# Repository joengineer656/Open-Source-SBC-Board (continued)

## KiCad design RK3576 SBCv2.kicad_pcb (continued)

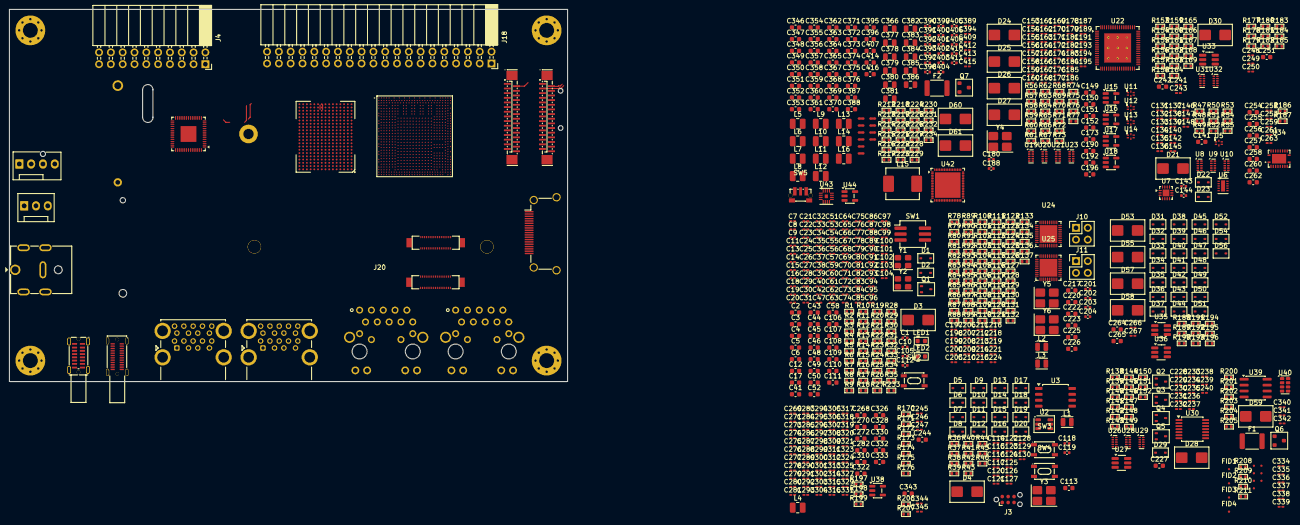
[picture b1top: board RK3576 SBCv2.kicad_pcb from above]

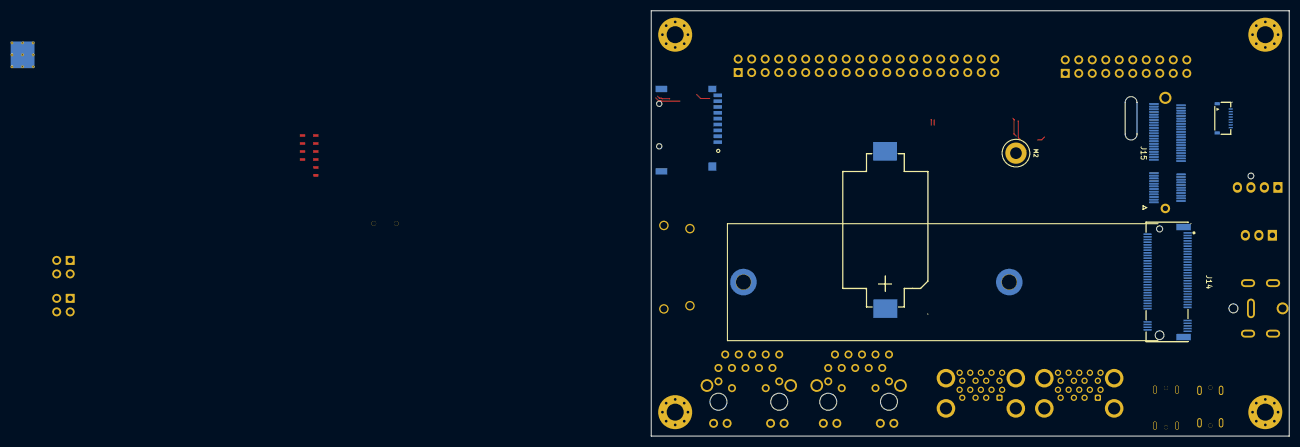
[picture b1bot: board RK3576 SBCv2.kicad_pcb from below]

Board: 8 copper layers, 120.0 x 80.0 mm, 840 parts (4 on the bottom side), 618 nets.

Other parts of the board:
C334, C335, C336, C337, C338, C339: 1u; C_0201_0603Metric_Pad0.64x0.40mm_HandSolder
J20: 513383474; SBC_UFS_EMMC_2x513383474

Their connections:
/RK3576 SOC/FSPI0_CLE/EMMC_DATA_STROBE: J20.23 (eMMC_DATA_STROBE); also elsewhere on the board
/RK3576 SOC/FSPI0_DS/EMMC_CLK_OUT: J20.12 (eMMC_CLKOUT); also elsewhere on the board
/RK3576 SOC/FSPI0_WPn/EMMC_nRST: J20.25 (~eMMC_RSTn); also elsewhere on the board
/RK3576 SOC/UFS.RX0_N: J20.60 (UFS_RX0_N); also elsewhere on the board
/RK3576 SOC/UFS.RX0_P: J20.61 (UFS_RX0_P); also elsewhere on the board
/RK3576 SOC/UFS.RX1_N: J20.57 (UFS_RX1_N); also elsewhere on the board
/RK3576 SOC/UFS.RX1_P: J20.58 (UFS_RX1_P); also elsewhere on the board
/RK3576 SOC/UFS.TX0_N: J20.66 (UFS_TX0_N); also elsewhere on the board
/RK3576 SOC/UFS.TX0_P: J20.67 (UFS_TX0_P); also elsewhere on the board
/RK3576 SOC/UFS.TX1_N: J20.63 (UFS_TX1_N); also elsewhere on the board
/RK3576 SOC/UFS.TX1_P: J20.64 (UFS_TX1_P); also elsewhere on the board
/RK3576 SOC/UFS_REF_{CLK}: J20.42 (UFS_REFCLK); also elsewhere on the board
/RK3576 SOC/UFS_nRST: J20.55 (~UFS_RSTn); also elsewhere on the board
VDDA_1V2_S0: C334.1, C335.1, J20.53 (VCC_1V2_UFS), J20.54 (VCC_1V2_UFS); also elsewhere on the board

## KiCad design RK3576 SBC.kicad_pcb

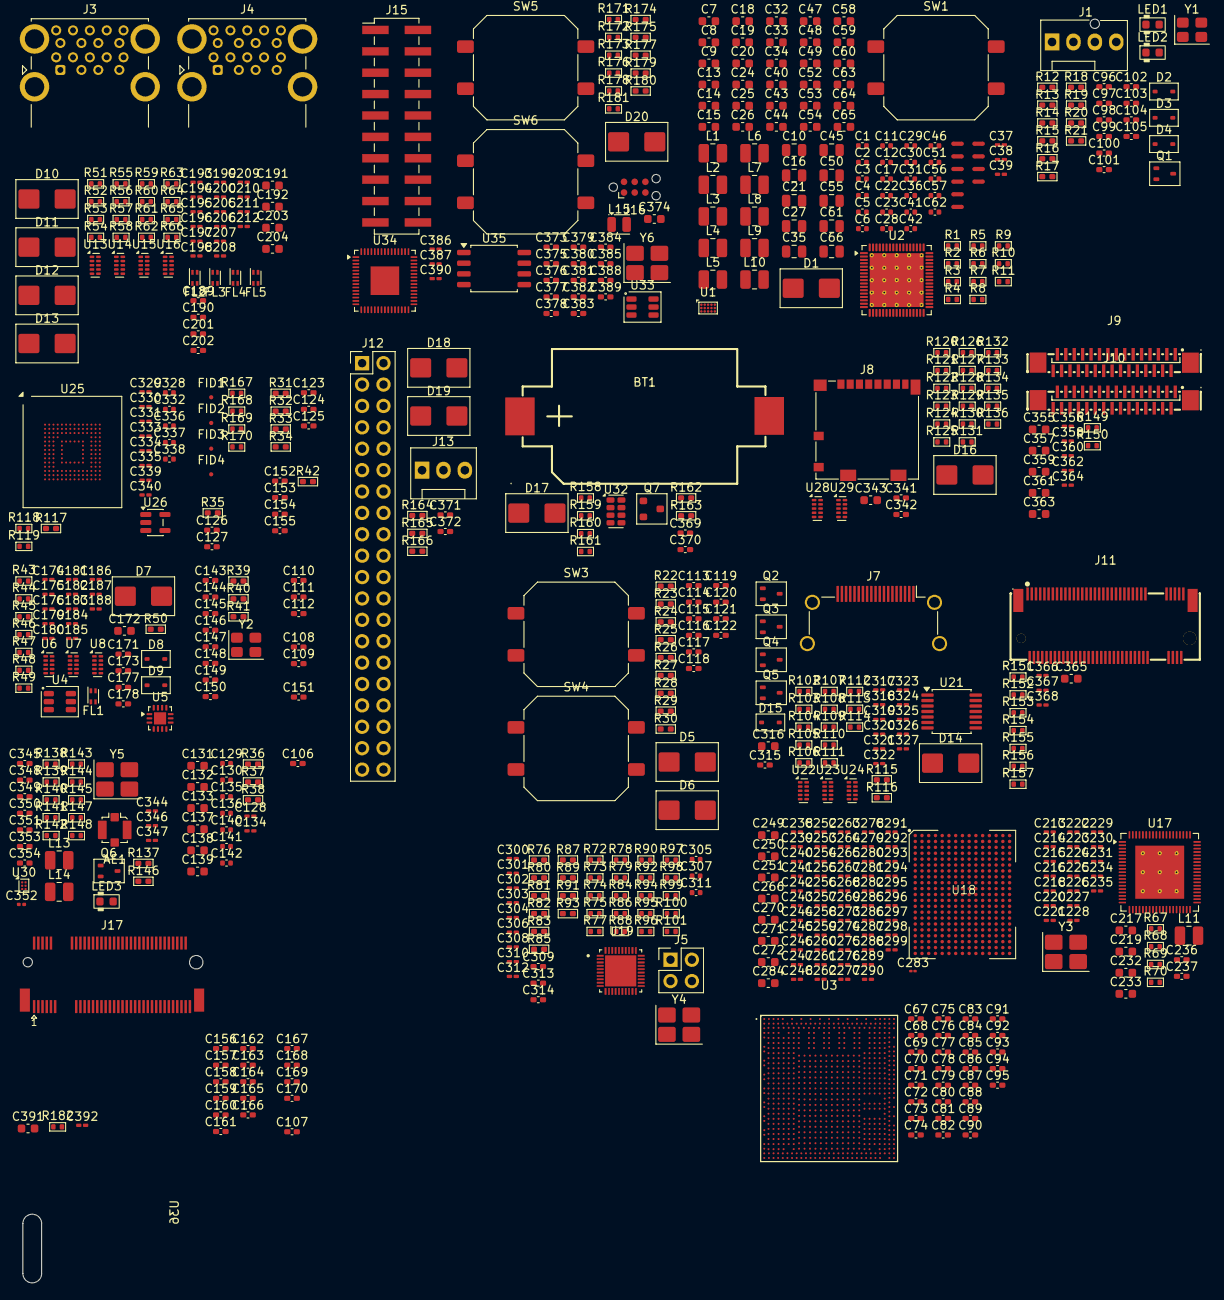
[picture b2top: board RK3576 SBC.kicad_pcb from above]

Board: 2 copper layers, 692 parts (0 on the bottom side), 309 nets, no tracks yet.

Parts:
AE1: Antenna_Shield; U.FL_Molex_MCRF_73412-0110_Vertical
BT1: BS-06-B4AA012; BAT-SMD_BS-06-B4AA012
C1, C2, C3, C4, C5, C6, C11, C12, C17, C22, C23, C28, C29, C30, C31, C36, C41, C42, C46, C51, C56, C57, C62, C336, C337, C338: 2.2u; C_0402_1005Metric
C7, C8, C9, C13, C14, C15, C18, C19, C20, C24, C25, C26, C32, C33, C34, C40, C43, C44, C47, C48, C49, C52, C53, C54, C58, C59, C60, C63, C64, C65, C131, C132, C133, C137, C138, C139, C172, C191, C192, C203, C204, C249, C250, C251, C266, C270, C271, C272, C284, C316, C343, C355, C357, C359, C361, C363, C365, C374: 22u; C_0603_1608Metric
C10, C16, C21, C27, C35, C45, C50, C55, C61, C66: 47u; C_0805_2012Metric
C37, C128, C134, C174, C175, C176, C213, C214, C215, C216, C218, C220, C221, C222, C224, C225, C226, C227, C228, C229, C230, C231, C234, C235, C238, C239, C240, C241, C242, C243, C244, C245, C246, C247, C248, C252, C253, C254, C255, C256, C257, C258, C259, C260, C261, C262, C263, C264, C265, C267, C268, C269, C273, C274, C275, C276, C277, C278, C279, C280, C281, C282, C285, C286, C287, C288, C289, C290, C291, C292, C293, C294, C295, C296, C297, C298, C299, C300, C301, C302, C303, C304, C306, C308, C310, C312, C326, C327, C329, C330, C331, C333, C334, C335, C339, C340, C344, C346, C347, C356, C358, C360, C362, C364, C366, C367, C368, C386, C387, C390, C392: 1u; C_0201_0603Metric_Pad0.64x0.40mm_HandSolder
C38, C39: 10n; C_0201_0603Metric_Pad0.64x0.40mm_HandSolder
C67, C77, C78, C79, C86, C87, C95, C152, C154: 10u; C_0402_1005Metric_Pad0.74x0.62mm_HandSolder
C68, C69, C70, C71, C72, C73, C74, C75, C76, C80, C81, C82, C83, C84, C85, C88, C89, C90, C91, C92, C93, C94, C96, C97, C98, C101, C102, C103, C104, C105, C106, C107, C108, C109, C110, C111, C113, C114, C115, C116, C117, C118, C119, C120, C121, C122, C123, C124, C125, C126, C127, C143, C144, C145, C146, C147, C148, C151, C153, C155, C156, C157, C158, C159, C160, C161, C162, C163, C164, C165, C166, C167, C168, C169, C170, C171, C173, C189, C190, C201, C202, C309, C315, C341, C342, C345, C348, C369, C370, C373, C375, C376, C377, C378, C379, C380, C381, C382, C383, C384, C385: 1u; C_0402_1005Metric_Pad0.74x0.62mm_HandSolder
C99, C100: 12pF; C_0402_1005Metric_Pad0.74x0.62mm_HandSolder
C112: 1n; C_0402_1005Metric_Pad0.74x0.62mm_HandSolder
C129, C130, C135, C136, C140, C141, C142: 1u; C_0402_1005Metric
C149, C150, C313, C314: 18pF; C_0402_1005Metric_Pad0.74x0.62mm_HandSolder
C177, C178: 200p; C_0402_1005Metric_Pad0.74x0.62mm_HandSolder
C179, C180, C181, C182, C183, C184, C185, C186, C187, C188, C193, C194, C195, C196, C197, C198, C199, C200, C205, C206, C207, C208, C209, C210, C211, C212: 100n; C_0201_0603Metric_Pad0.64x0.40mm_HandSolder
C217, C219, C232, C233, C391: 10u; C_0603_1608Metric
C223: 10u; C_0201_0603Metric_Pad0.64x0.40mm_HandSolder
C236, C237: 20pF; C_0402_1005Metric_Pad0.74x0.62mm_HandSolder
C283: 1u; C_01005_0402Metric
C305, C307, C311, C328, C332: 10u; C_0402_1005Metric
C317, C318, C319, C320, C321, C322, C323, C324, C325: 220n; C_0201_0603Metric_Pad0.64x0.40mm_HandSolder
C349, C350: DNP; C_0402_1005Metric_Pad0.74x0.62mm_HandSolder
C351: 8p; C_0402_1005Metric_Pad0.74x0.62mm_HandSolder
C352: 10u; C_0201_0603Metric
C353, C354: 10pF; C_0402_1005Metric_Pad0.74x0.62mm_HandSolder
C371, C372: 22u; C_0402_1005Metric_Pad0.74x0.62mm_HandSolder
C388, C389: 34pF; C_0402_1005Metric_Pad0.74x0.62mm_HandSolder
D1, D5, D6, D7, D10, D11, D12, D13, D14, D16, D17, D18, D19, D20: SMBJ5.0CA; D_SMB_TVS
D2, D3, D4, D8, D9, D15: PESD5V0S1BA; D_SOD-323_TVS
FID1, FID2, FID3, FID4: Fiducial; Fiducial_0.5mm_Mask1.5mm
FL1, FL2, FL3, FL4, FL5: 0603USB-142; L_CommonModeChoke_Coilcraft_0603USB
J1: Conn_01x04_Pin; FanPinHeader_1x04_P2.54mm_Vertical
J3, J4: USB3_A_Stacked; USB3_A_Molex_48406-0001_Horizontal_Stacked
J5: POE Connector; PinHeader_2x02_P2.54mm_Vertical
J7: HDMI_A; HDMI_A_Amphenol_10029449-x01xLF_Horizontal
J8: Micro_SD_Card_Det1; microSD_HC_Molex_104031-0811
J9: CSI Connector; FPC-SMD_30P-L20.5-W2.0-P0.50
J10: DSI Connector; FPC-SMD_30P-L20.5-W2.0-P0.50
J11: 1-2199230-5; PCIE-SMD_75P-P0.50_1-2199230-5
J12: Raspberry_Pi_4; 40-pin GPIO Header for Raspberry Pi
J13: JST_03; FanPinHeader_1x03_P2.54mm_Vertical
J15: Conn_02x10_Counter_Clockwise; PinHeader_2x10_P2.54mm_Vertical_SMD
J16: Conn_ARM_SWD_TagConnect_TC2030-NL; Tag-Connect_TC2030-IDC-NL_2x03_P1.27mm_Vertical
J17: TE_2199230-3
L1, L2, L3, L4, L5, L6, L7, L8, L9, L10: FTC252012SR24MBCA; L_1008_2520Metric
L11, L13, L14: ???; L_1008_2520Metric
L15: YL201209-3R3K; L_Coilcraft_0805HQ_2012Metric
LED1, LED2: LED_0603_Red; LED_0603_1608Metric
LED3: LED_0603_Yellow; LED_0603_1608Metric
NT1, NT2, NT3, NT4, NT5, NT6, NT7, NT8, NT9, NT10: NetTie_2; NetTie-2_SMD_Pad0.5mm
Q1, Q2, Q3, Q4, Q5, Q6: 2SK3018; SOT-323_SC-70
Q7: AO3401A; SOT-23
R1, R44, R46, R47, R48, R49, R111, R119, R121, R144, R145, R151, R152, R157, R158, R161, R172, R178, R182: 10k; R_0402_1005Metric
R2, R5, R7, R9, R11, R43, R54, R56, R62, R64, R67, R68, R112, R122, R171: 100k; R_0402_1005Metric
R3: 49.9k; R_0402_1005Metric
R4, R6, R84, R86, R88, R90, R92, R94, R130, R131, R132, R133, R134, R135, R136, R138, R139, R140, R141, R142, R143, R153, R154, R155, R156: 22R; R_0402_1005Metric
R8: 2k; R_0402_1005Metric
R10: 110k; R_0402_1005Metric
R12, R50, R81, R82, R83, R85, R87, R89, R91, R93, R116, R117, R137, R146, R177, R180: 0R; R_0402_1005Metric_Pad0.72x0.64mm
R13, R25, R26, R27, R28, R29, R30, R115: 10k; R_0402_1005Metric_Pad0.72x0.64mm
R14, R19, R20, R21, R36, R37, R38, R40, R162, R163, R166: 22R; R_0402_1005Metric_Pad0.72x0.64mm
R15: 220R; R_0402_1005Metric_Pad0.72x0.64mm
R16, R17, R179: 1k; R_0402_1005Metric_Pad0.72x0.64mm
R18: 100ki; R_0402_1005Metric_Pad0.72x0.64mm
R22: 6.8k; R_0402_1005Metric_Pad0.72x0.64mm
R23: 23.2k; R_0402_1005Metric_Pad0.72x0.64mm
R24: 88.7k; R_0402_1005Metric_Pad0.72x0.64mm
R31, R33: 4.7k; R_0402_1005Metric_Pad0.72x0.64mm
R32, R34: 200R; R_0402_1005Metric_Pad0.72x0.64mm
R35, R39, R42: 8.2k; R_0402_1005Metric_Pad0.72x0.64mm
R41: 510k; R_0402_1005Metric_Pad0.72x0.64mm
R45, R72, R73, R74, R77, R78, R79, R95, R96, R97, R98, R123, R124, R125, R126, R127, R128, R129, R148, R173: 4.7k; R_0402_1005Metric
R51, R52, R59, R60, R102, R113, R114, R120, R149, R150, R159, R160: 2.2k; R_0402_1005Metric
R53, R55, R61, R63: 15k; R_0402_1005Metric
R57, R58, R65, R66, R69, R167, R168, R169, R170: 0R; R_0402_1005Metric
R70: 6.2k; R_0402_1005Metric
R75: 2.49k; R_0402_1005Metric
R76, R80: 510R; R_0402_1005Metric_Pad0.72x0.64mm
R99, R100, R101: 1.2k; R_0402_1005Metric
R103, R104, R105, R106, R107, R108, R109, R110: 590R; R_0402_1005Metric
R118: 35k; R_0402_1005Metric
R147, R181: 1k; R_0402_1005Metric
R164, R165: 10K; R_0402_1005Metric_Pad0.72x0.64mm
R174, R175: 5.1k; R_0402_1005Metric_Pad0.72x0.64mm
R176: 5.1k; R_0402_1005Metric
SW1, SW3, SW4, SW5, SW6: SW_Push; SW_Push_1P1T_NO_CK_PTS125Sx85SMTR
U1: MAX14713EWL+T; WLP-15_MAX14713
U2: RK806S-5; QFN-68-1EP_8x8mm_P0.4mm_EP6.4x6.4mm_ThermalVias
U3: RK3576; FCCSP-698_L17.2-W16.1-TL_RK3576
U4, U33: ETA7014S2G; TSOT-23-6
U5: FUSB302BMPX; WQFN-14-1EP_2.5x2.5mm_P0.5mm_EP1.45x1.45mm
U6, U7, U8, U13, U14, U15, U16, U22, U23, U24, U28, U29: TPD4E05U06DQA; USON-10_2.5x1.0mm_P0.5mm
U17: RTS5411S-GR; QFN-76-1EP_9x9mm_P0.4mm_EP5.81x6.31mm_ThermalVias
U18: MT62F1G32D4DR-031; LPDDR5 BGA 315
U19: RTL8211F-CG; QFN40P500X500X90-41N
U21: TXB0104PW; TSSOP-14_4.4x5mm_P0.65mm
U25: HN8T05DEHK-X073; LFBGA-153_11.5x13mm_Layout14x14_P0.5mm
U26: TLV75801PDBV; SOT-23-5
U30: BGS12P2L6E6327XTSA1; Infineon_PG-TSNP-6-10_0.7x1.1mm_0.7x1.1mm_P0.4mm
U32: RV-3028-C7; MicroCrystal_C7_SON-8_1.5x3.2mm_P0.9mm
U34: RP2350A; QFN-60-1EP_7x7mm_P0.4mm_EP3.4x3.4mm
U35: W25Q128JVS; SOIC-8_5.3x5.3mm_P1.27mm
U36: 0.96 OLED Display 8 pins; FFC-SMD_8P-P0.50_AFC42-S08FMA-1H_BOTTOM
Y1: TXM24M0004322FBCDO00T; Crystal_SMD_3225-4Pin_3.2x2.5mm
Y2: XTM32026000FT00351001; Crystal_SMD_3225-4Pin_3.2x2.5mm
Y3: K3A120002010; Crystal_SMD_3225-4Pin_3.2x2.5mm_HandSoldering
Y4: SX32Y025000BC1T001; Crystal_SMD_3225-4Pin_3.2x2.5mm_HandSoldering
Y5: T3225374MDBDE2X; Crystal_SMD_3225-4Pin_3.2x2.5mm_HandSoldering
Y6: TAXM12M4RLBDDT2T; Crystal_SMD_3225-4Pin_3.2x2.5mm_HandSoldering

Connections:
1.1v: C376.1, C377.1, C378.1, L15.1, U34.6 (DVDD), U34.23 (DVDD), U34.39 (DVDD), U34.50 (VREG_FB)
+1.2V_{HUB}: C213.1, C214.1, C215.1, C216.1, C217.1, C220.1, C221.1, C222.1, L11.1, U17.3 (DV12), U17.4 (DV33), U17.22 (DV33), U17.48 (DV33), U17.49 (DV12), U17.50 (DV12), U17.73 (DV33)
+1.8V: C346.1, R95.1, R96.1, R97.1, R98.1, R123.1, R124.1, R125.1, R126.1, R127.1, R128.1, R129.1, U30.4 (VDD)
+3.3V: LED3.2 (A), R76.2, R77.1, R78.1
+3.3V_{GPIO}: C372.1, J12.1 (3V3), J12.17 (3V3)
+3.3V_{HUB}: C218.1, C219.1, C223.1, C224.1, C225.1, C226.1, C227.1, C228.1, C229.1, C230.1, C231.1, U17.7 (AV12), U17.13 (AV12), U17.19 (AV12), U17.25 (AV12), U17.31 (AV12), U17.52 (SWR_OUT), U17.58 (AV12), U17.64 (AV12), U17.70 (AV12)
+5V_{GPIO}: C371.1, J12.2 (5V), J12.4 (5V)
+5V_{HDMI}: C316.1, C326.1, D14.2 (A), J7.18 (+5V), U21.14 (VCCB)
+5v: C7.1, C13.1, C18.1, C24.1, C32.1, C40.1, C47.1, C52.1, C58.1, C63.1, U2.1 (VCC9), U2.7 (VCC8), U2.22 (VCC4), U2.27 (VCC10), U2.28 (VCC6), U2.33 (VCC2), U2.34 (VCC2), U2.43 (VCC7), U2.44 (VCC5), U2.52 (VCC1), U2.53 (VCC1), U2.54 (VCC3)
/4x USB Hub/Crystal_{HUB}_IN: C236.1, U17.74 (XTLI), Y3.1
/4x USB Hub/Crystal_{HUB}_OUT: C237.1, U17.75 (XTLO), Y3.3
/40Pin Header/SARADC_VIN4_IN: R164.1, R165.1
/Ethernet/Crystal_{ETH}_IN: C313.1, U19.36 (XTAL_IN), Y4.1
/Ethernet/Crystal_{ETH}_OUT: C314.1, U19.37 (XTAL_OUT/EXT_CLK), Y4.3
/Ethernet/ETH_{PHY}_INT: R74.2, U19.31 (INTB/PMEB)
/Ethernet/ETH_{PHY}_LED0: R77.2, U19.32 (LED0/CFG_EXT)
/Ethernet/ETH_{PHY}_LED1: R79.1, U19.33 (LED1/CFG_LDO0)
/Ethernet/ETH_{PHY}_LED2: R78.2, U19.34 (LED2/CFG_LDO1)
/Ethernet/ETH_{PHY}_MDIO: R73.2, U19.14 (MDIO)
/Ethernet/ETH_{PHY}_RESET: C312.1, R72.2, U19.12 (PHYRSTB)
/Ethernet/ETH_{PHY}_RXC: R92.2, R100.1
/Ethernet/ETH_{PHY}_RXCTL: R94.2, R101.1
/Ethernet/ETH_{PHY}_RXD0: R84.2, R95.2
/Ethernet/ETH_{PHY}_RXD1: R86.2, R96.2
/Ethernet/ETH_{PHY}_RXD2: R88.2, R97.2, R99.1
/Ethernet/ETH_{PHY}_RXD3: R90.2, R98.2
/HDMI/CHDMI_CEC: J7.13 (CEC), U21.13 (B1), U24.1 (D1+)
/HDMI/CHDMI_CK_N: C324.2, J7.12 (CK-), R103.1, U23.5 (D2-)
/HDMI/CHDMI_CK_P: C323.2, J7.10 (CK+), R104.1, U23.4 (D2+)
/HDMI/CHDMI_D0_N: C322.2, J7.9 (D0-), R105.1, U23.2 (D1-)
/HDMI/CHDMI_D0_P: C321.2, J7.7 (D0+), R106.1, U23.1 (D1+)
/HDMI/CHDMI_D1_N: C320.2, J7.6 (D1-), R107.1, U22.5 (D2-)
/HDMI/CHDMI_D1_P: C319.2, J7.4 (D1+), R108.1, U22.4 (D2+)
/HDMI/CHDMI_D2_N: C318.2, J7.3 (D2-), R109.1, U22.2 (D1-)
/HDMI/CHDMI_D2_P: C317.2, J7.1 (D2+), R110.1, U22.1 (D1+)
/HDMI/CHDMI_HPD: D15.2 (A), J7.19 (HPD), U21.10 (B4)
/HDMI/CHDMI_UTILITY: C325.2, J7.14 (UTILITY), U24.5 (D2-)
/HDMI/CSCL: J7.15 (SCL), U21.12 (B2), U24.2 (D1-)
/HDMI/CSDA: J7.16 (SDA), U21.11 (B3), U24.4 (D2+)
/HDMI/HDMI_TX_ON: Q2.1 (G), Q3.1 (G), Q4.1 (G), Q5.1 (G)
/HDMI/HDMI_TX_SCL: R113.2, U21.3 (A2)
/HDMI/HDMI_TX_SDA: R114.2, U21.4 (A3)
/MIPI/I2C4_SCL_M3_MIPI_CAM2: J9.23, R150.2
/MIPI/I2C4_SDA_M3_MIPI_CAM2: J9.24, R149.2
/OLED Screen/OLED_RESET: R182.2, U36.3 (RESET)
/PCIe/PCIE0_RESETn: R151.2, R153.2
/PCIe/PCIe_PWR_EN: R152.2, R156.2, R157.1
/Power/PMIC_INT_L: R1.2, U2.19 (INT)
/Power/PMIC_PWRON_L: D1.2 (A), R6.2, SW1.1
/RK3576/GPIO0/JTAG_TCK_M1 & UART0_TX_M0: D2.2 (A), J1.1, R19.2
/RK3576/GPIO0/JTAG_TMS_M1 & UART0_RX_M0: D3.2 (A), J1.2, R20.2
/RK3576/GPIO0/RESET_L: C97.1, R12.1, R13.2, U3.W28 (NPOR)
/RK3576/GPIO0/TSADC_CTRL_M0: R12.2, U3.1R24 (TSADC_CTRL_M0)
/RK3576/GPIO0/USER_LED: R17.1, U3.1AA23 (SAI0_SDI3_M1)
/RK3576/GPIO4/HDMI_HPD: C112.1, U3.AK2 (DSM_AUD_LN_M1)
/RK3576/HDMI PHY/HDMI_REXT: R42.1, U3.1AA20 (HDMI_TX_REXT)
/RK3576/RK3576 UFS/UFS3.1_TX_REXT: R39.1, U3.2R2 (UFS_TX_REXT)
/RK3576/RK3576 USB3 DP1.4/USB_{OTG}_REXT: R35.1, U3.2T7 (USB3_OTG0_REXT)
/RK3576/SARADC/SARADC_VIN0_BOOT: C115.1, D5.2 (A), R25.2, SW3.1, U3.A25 (SARADC_IN0_BOOT)
/RK3576/SARADC/SARADC_VIN1_KEY/RECOVERY: C116.1, D6.2 (A), R26.2, SW4.1, U3.1A22 (SARADC_IN1)
/RK3576/SARADC/SARADC_VIN2_HW_ID: C117.1, R28.2, R30.1, U3.1B19 (SARADC_IN2)
/RK3576/SARADC/SARADC_VIN3_HP_HOOK: C118.1, U3.1C19 (SARADC_IN3)
/RK3576/SARADC/SARADC_VIN4_IN: C119.1, U3.1E18 (SARADC_IN4)
/RK3576/SARADC/SARADC_VIN5_BOM_ID: C120.1, R27.2, R29.1, U3.1D19 (SARADC_IN5)
/RK3576/SARADC/SARADC_VIN6: C121.1, U3.1D21 (SARADC_IN6)
/RK3576/SARADC/SARADC_VIN7_DC: C122.1, U3.1E19 (SARADC_IN7)
/RP2350A/ADC0_{MCU}: J15.15, U34.40 (GPIO26/ADC0)
/RP2350A/ADC1_{MCU}: J15.16, U34.41 (GPIO27/ADC1)
/RP2350A/ADC2_{MCU}: J15.17, U34.42 (GPIO28/ADC2)
/RP2350A/ADC3_{MCU}: J15.18, U34.43 (GPIO29/ADC3)
/RP2350A/Crystal_{MCU}_IN: C388.1, U34.21 (XIN), Y6.1
/RP2350A/Crystal_{MCU}_OUT: C389.1, U34.22 (XOUT), Y6.3
/RP2350A/Flash_{MCU}_CLK: U34.56 (QSPI_SCLK), U35.6 (CLK)
/RP2350A/Flash_{MCU}_SD0: U34.57 (QSPI_SD0), U35.5 (DI/IO_{0})
/RP2350A/Flash_{MCU}_SD1: U34.59 (QSPI_SD1), U35.2 (DO/IO_{1})
/RP2350A/Flash_{MCU}_SD2: U34.58 (QSPI_SD2), U35.3 (~WP/IO_{2})
/RP2350A/Flash_{MCU}_SD3: U34.55 (QSPI_SD3), U35.7 (~HOLD/~RESET/IO_{3})
/RP2350A/Flash_{MCU}_SS: R180.2, U34.60 (~QSPI_SS)
/RP2350A/GPIO_{MCU}_6: J15.7, U34.9 (GPIO6)
/RP2350A/GPIO_{MCU}_7: J15.8, U34.10 (GPIO7)
/RP2350A/I2C0_{MCU}_SCL: J15.6, U34.8 (GPIO5)
/RP2350A/I2C0_{MCU}_SDA: J15.5, U34.7 (GPIO4)
/RP2350A/Reset_{MCU}: J16.3 (~RESET), R178.2, R179.2, U34.26 (RUN)
/RP2350A/SPI0_{MCU}_CS: J15.12, U34.28 (GPIO17)
/RP2350A/SPI0_{MCU}_SCK: J15.13, U34.29 (GPIO18)
/RP2350A/SPI0_{MCU}_SDI: J15.11, U34.27 (GPIO16)
/RP2350A/SPI0_{MCU}_SDO: J15.14, U34.31 (GPIO19)
/RP2350A/SWCLK_{MCU}: J16.4 (SWCLK), U34.24 (SWCLK)
/RP2350A/SWDIO_{MCU}: J16.2 (SWDIO), U34.25 (SWDIO)
/RP2350A/UART1_{MCU}_RX: J15.10, U34.13 (GPIO9)
/RP2350A/UART1_{MCU}_TX: J15.9, U34.12 (GPIO8)
/RP2350A/Vdet_USB_{MCU}: R172.2, R173.1
/RTC/I2C2_SCL_M0_CC_RTC: R159.2, U32.3 (SCL)
/RTC/I2C2_SDA_M0_CC_RTC: R160.2, U32.4 (SDA)
/USB3.2 Host/CUSB_{HOST1}_D_N: FL2.1, J3.2 (D1-)
/USB3.2 Host/CUSB_{HOST1}_D_P: FL2.4, J3.3 (D1+)
/USB3.2 Host/CUSB_{HOST1}_SSRX1_N: C193.2, J3.5 (SSRX1-), U15.1 (D1+)
/USB3.2 Host/CUSB_{HOST1}_SSRX1_P: C195.2, J3.6 (SSRX1+), U15.2 (D1-)
/USB3.2 Host/CUSB_{HOST1}_SSTX1_N: C197.2, J3.8 (SSTX1-), U15.4 (D2+)
/USB3.2 Host/CUSB_{HOST1}_SSTX1_P: C199.2, J3.9 (SSTX1+), U15.5 (D2-)
/USB3.2 Host/CUSB_{HOST2}_D_N: FL4.1, J3.11 (D2-)
/USB3.2 Host/CUSB_{HOST2}_D_P: FL4.4, J3.12 (D2+)
/USB3.2 Host/CUSB_{HOST2}_SSRX1_N: C205.2, J3.14 (SSRX2-), U16.1 (D1+)
/USB3.2 Host/CUSB_{HOST2}_SSRX1_P: C207.2, J3.15 (SSRX2+), U16.2 (D1-)
/USB3.2 Host/CUSB_{HOST2}_SSTX1_N: C209.2, J3.17 (SSTX2-), U16.4 (D2+)
/USB3.2 Host/CUSB_{HOST2}_SSTX1_P: C211.2, J3.18 (SSTX2+), U16.5 (D2-)
/USB3.2 Host/CUSB_{HOST3}_D_N: FL3.1, J4.2 (D1-)
/USB3.2 Host/CUSB_{HOST3}_D_P: FL3.4, J4.3 (D1+)
/USB3.2 Host/CUSB_{HOST3}_SSRX1_N: C194.2, J4.5 (SSRX1-), U13.1 (D1+)
/USB3.2 Host/CUSB_{HOST3}_SSRX1_P: C196.2, J4.6 (SSRX1+), U13.2 (D1-)
/USB3.2 Host/CUSB_{HOST3}_SSTX1_N: C198.2, J4.8 (SSTX1-), U13.4 (D2+)
/USB3.2 Host/CUSB_{HOST3}_SSTX1_P: C200.2, J4.9 (SSTX1+), U13.5 (D2-)
/USB3.2 Host/CUSB_{HOST4}_D_N: FL5.1, J4.11 (D2-)
/USB3.2 Host/CUSB_{HOST4}_D_P: FL5.4, J4.12 (D2+)
/USB3.2 Host/CUSB_{HOST4}_SSRX1_N: C206.2, J4.14 (SSRX2-), U14.1 (D1+)
/USB3.2 Host/CUSB_{HOST4}_SSRX1_P: C208.2, J4.15 (SSRX2+), U14.2 (D1-)
/USB3.2 Host/CUSB_{HOST4}_SSTX1_N: C210.2, J4.17 (SSTX2-), U14.4 (D2+)
/USB3.2 Host/CUSB_{HOST4}_SSTX1_P: C212.2, J4.18 (SSTX2+), U14.5 (D2-)
/USB3.2 Host/USB_{HOST}_PWREN_H: R51.2, R52.2, R59.2, R60.2
/USB3.2 OTG/CUSB_{OTG}_D_N: FL1.1, U6.1 (D1+)
/USB3.2 OTG/CUSB_{OTG}_D_P: FL1.4, U6.2 (D1-)
/USB3.2 OTG/CUSB_{OTG}_RX1_N: C179.2, U6.4 (D2+)
/USB3.2 OTG/CUSB_{OTG}_RX1_P: C180.2, U6.5 (D2-)
/USB3.2 OTG/CUSB_{OTG}_RX2_N: C183.2, U7.4 (D2+)
/USB3.2 OTG/CUSB_{OTG}_RX2_P: C184.2, U7.5 (D2-)
/USB3.2 OTG/CUSB_{OTG}_SUB1: C187.2, R46.1, R48.1, U8.4 (D2+)
/USB3.2 OTG/CUSB_{OTG}_SUB2: C188.2, R47.1, R49.1, U8.5 (D2-)
/USB3.2 OTG/CUSB_{OTG}_TX1_N: C181.2, U7.1 (D1+)
/USB3.2 OTG/CUSB_{OTG}_TX1_P: C182.2, U7.2 (D1-)
/USB3.2 OTG/CUSB_{OTG}_TX2_N: C185.2, U8.1 (D1+)
/USB3.2 OTG/CUSB_{OTG}_TX2_P: C186.2, U8.2 (D1-)
/USB3.2 OTG/USB_{OTG}_CC1: C177.1, D8.2 (A), U5.10 (CC1), U5.11 (CC1)
/USB3.2 OTG/USB_{OTG}_CC2: C178.1, D9.2 (A), U5.1 (CC2), U5.14 (CC2)
/USB3.2 OTG/Vdet_USB_{OTG}: R44.2, R45.1
/WIFI & Blutooth/WIFI_BT_ANT_CTRL: R145.1, U30.6 (CTRL)
/uSD Card/J_uSD_CLK: J8.5 (CLK), R133.2, U28.5 (D2-)
/uSD Card/J_uSD_CMD: J8.3 (CMD), R132.2, U28.4 (D2+)
/uSD Card/J_uSD_D0: J8.7 (DAT0), R134.2, U29.1 (D1+)
/uSD Card/J_uSD_D1: J8.8 (DAT1), R135.2, U29.2 (D1-)
/uSD Card/J_uSD_D2: J8.1 (DAT2), R130.2, U28.1 (D1+)
/uSD Card/J_uSD_D3: J8.2 (DAT3/CD), R131.2, U28.2 (D1-)
/uSD Card/J_uSD_DET: J8.9 (DET), R136.2, U29.4 (D2+)
/uSD Card/uSD_CLK: R126.2, R133.1
/uSD Card/uSD_CMD: R125.2, R132.1
/uSD Card/uSD_D0: R127.2, R134.1
/uSD Card/uSD_D1: R128.2, R135.1
/uSD Card/uSD_D2: R123.2, R130.1
/uSD Card/uSD_D3: R124.2, R131.1
/uSD Card/uSD_DET: R129.2, R136.1
ETH_{PHY}_1V0: C300.1, C301.1, C302.1, C303.1, C310.1, C311.1, U19.3 (AVDD10), U19.8 (AVDD10), U19.21 (DVDD10), U19.38 (AVDD10)
GND: AE1.2 (Shield), BT1.2 (-), C1.2, C2.2, C3.2, C4.2, C5.2, C6.2, C7.2, C8.2, C9.2, C10.2, C11.2, C12.2, C13.2, C14.2, C15.2, C16.2, C17.2, C18.2, C19.2, C20.2, C21.2, C22.2, C23.2, C24.2, C25.2, C26.2, C27.2, C28.2, C29.2, C30.2, C31.2, C32.2, C33.2, C34.2, C35.2, C36.2, C37.2, C38.2, C39.2, C40.2, C41.2, C42.2, C46.2, C47.2, C51.2, C52.2, C56.2, C57.2, C58.2, C62.2, C63.2, C67.2, C68.2, C69.2, C70.2, C71.2, C72.2, C73.2, C74.2, C75.2, C76.2, C77.2, C78.2, C79.2, C80.2, C81.2, C82.2, C83.2, C84.2, C85.2, C86.2, C87.2, C88.2, C89.2, C90.2, C91.2, C92.2, C93.2, C94.2, C95.2, C96.2, C97.2, C98.2, C99.2, C100.2, C101.2, C102.2, C103.2, C104.2, C105.2, C106.2, C107.2, C108.2, C109.2, C110.2, C111.2, C112.2, C113.2, C114.2, C115.2, C116.2, C117.2, C118.2, C119.2, C120.2, C121.2, C122.2, C123.2, C124.2, C125.2, C126.2, C127.2, C128.2, C129.2, C130.2, C131.2, C132.2, C133.2, C134.2, C135.2, C136.2, C137.2, C138.2, C139.2, C140.2, C141.2, C142.2, C143.2, C144.2, C145.2, C146.2, C147.2, C148.2, C149.2, C150.2, C151.2, C152.2, C153.2, C154.2, C155.2, C156.2, C157.2, C158.2, C159.2, C160.2, C161.2, C162.2, C163.2, C164.2, C165.2, C166.2, C167.2, C168.2, C169.2, C170.2, C171.2, C172.2, C173.2, C174.2, C175.2, C176.2, C177.2, C178.2, C189.2, C190.2, C191.2, C192.2, C201.2, C202.2, C203.2, C204.2, C213.2, C214.2, C215.2, C216.2, C217.2, C218.2, C219.2, C220.2, C221.2, C222.2, C223.2, C224.2, C225.2, C226.2, C227.2, C228.2, C229.2, C230.2, C231.2, C232.2, C233.2, C234.2, C235.2, C236.2, C237.2, C238.2, C239.2, C240.2, C241.2, C242.2, C243.2, C244.2, C245.2, C246.2, C247.2, C248.2, C249.2, C250.2, C251.2, C252.2, C253.2, C254.2, C255.2, C256.2, C257.2, C258.2, C259.2, C260.2, C261.2, C262.2, C263.2, C264.2, C265.2, C266.2, C267.2, C268.2, C269.2, C270.2, C271.2, C272.2, C273.2, C274.2, C275.2, C276.2, C277.2, C278.2, C279.2, C280.2, C281.2, C282.2, C283.2, C284.2, C285.2, C286.2, C287.2, C288.2, C289.2, C290.2, C291.2, C292.2, C293.2, C294.2, C295.2, C296.2, C297.2, C298.2, C299.2, C300.2, C301.2, C302.2, C303.2, C304.2, C305.2, C306.2, C307.2, C308.2, C309.2, C310.2, C311.2, C312.2, C313.2, C314.2, C315.2, C316.2, C326.2, C327.2, C328.2, C329.2, C330.2, C331.2, C332.2, C333.2, C334.2, C335.2, C336.2, C337.2, C338.2, C339.2, C340.2, C341.2, C342.2, C343.2, C344.2, C345.2, C346.2, C347.2, C348.2, C349.2, C350.2, C351.2, C352.2, C353.2, C354.2, C355.2, C356.2, C357.2, C358.2, C359.2, C360.2, C361.2, C362.2, C363.2, C364.2, C365.2, C366.2, C369.2, C370.2, C371.2, C372.2, C373.2, C374.2, C375.2, C376.2, C377.2, C378.2, C379.2, C380.2, C381.2, C382.2, C383.2, C384.2, C385.2, C386.2, C387.2, C388.2, C389.2, C390.2, C391.2, C392.2, D1.1 (K), D2.1 (K), D3.1 (K), D4.1 (K), D5.1 (K), D6.1 (K), D7.1 (K), D8.1 (K), D9.1 (K), D10.1 (K), D11.1 (K), D12.1 (K), D13.1 (K), D14.1 (K), D15.1 (K), D16.1 (K), D17.1 (K), D18.1 (K), D19.1 (K), D20.1 (K), J1.4, J3.4 (GND1), J3.7 (DRAIN1), J3.13 (GND2), J3.16 (DRAIN2), J4.4 (GND1), J4.7 (DRAIN1), J4.13 (GND2), J4.16 (DRAIN2), J7.2 (D2S), J7.5 (D1S), J7.8 (D0S), J7.11 (CKS), J7.17 (GND), J8.6 (VSS), J8.SH (SHIELD), J9.1, J9.4, J9.7, J9.10, J9.13, J9.16, J9.19, J9.27, J10.1, J10.4, J10.7, J10.10, J10.13, J10.16, J10.24, J10.25, J11.1 (GND), J11.3 (GND), J11.5 (GND), J11.7 (GND), J11.9 (GND), J11.11 (GND), J11.13 (GND), J11.15 (GND), J11.18 (GND), J11.20 (GND), J11.21 (GND), J11.23 (GND), J11.26 (GND), J11.28 (GND), J11.29 (GND), J11.31 (GND), J11.34 (GND), J11.36 (GND), J11.37 (GND), J11.39 (GND), J11.42 (GND), J11.44 (GND), J11.46 (GND), J11.48 (GND), J11.49 (GND), J11.51 (GND), J11.53 (GND), J11.55 (GND), J11.57 (GND), J12.6 (GND), J12.9 (GND), J12.14 (GND), J12.20 (GND), J12.25 (GND), J12.30 (GND), J12.34 (GND), J12.39 (GND), J13.3, J15.19, J15.20, J16.5 (GND), L13.2, LED2.1 (K), Q1.2 (S), Q2.2 (S), Q3.2 (S), Q4.2 (S), Q5.2 (S), Q6.2 (S), R5.2, R7.2, R9.2, R11.2, R18.2, R22.1, R23.1, R24.1, R29.2, R30.2, R32.2, R34.2, R35.2, R36.2, R39.2, R42.2, R45.2, R46.2, R47.2, R50.2, R53.2, R54.2, R55.2, R56.2, R57.2, R58.2, R61.2, R62.2, R63.2, R64.2, R65.2, R66.2, R68.2, R69.2, R70.2, R75.2, R79.2, R99.2, R100.2, R101.2, R111.2, R112.2, R115.2, R116.2, R119.2, R121.2, R122.2, R145.2, R157.2, R158.2, R165.2, R167.2, R168.2, R169.2, R170.2, R173.2, R174.2, R175.2, R177.2, SW1.2, SW3.2, SW4.2, SW5.1, SW6.1, U1.C3 (GND), U2.31 (FB6), U2.47 (FB5), U2.66 (FB9), U2.69 (EP), U3.1A2 (VSS[163]), U3.1A3 (VSS[163]), U3.1AA2 (VSS[163]), U3.1AA4 (VSS[163]), U3.1AA21 (VSS[163]), U3.1AA24 (VSS[163]), U3.1AB2 (VSS[163]), U3.1AB5 (VSS[163]), U3.1AB6 (VSS[163]), U3.1AB20 (AVSS[77]), U3.1AB21 (AVSS[77]), U3.1AB22 (AVSS[77]), U3.1AB23 (AVSS[77]), U3.1AB24 (AVSS[77]), U3.1AC1 (VSS[163]), U3.1AC2 (VSS[163]), U3.1AC3 (VSS[163]), U3.1AC4 (VSS[163]), U3.1AC5 (VSS[163]), U3.1AC20 (AVSS[77]), U3.1AC21 (AVSS[77]), U3.1AC24 (AVSS[77]), U3.1AD3 (VSS[163]), U3.1AD20 (AVSS[77]), U3.1AD23 (AVSS[77]), U3.1AD24 (AVSS[77]), U3.1AE3 (VSS[163]), U3.1AE4 (AVSS[77]), U3.1AE6 (AVSS[77]), U3.1AE20 (AVSS[77]), U3.1AE21 (AVSS[77]), U3.1AE23 (AVSS[77]), U3.1B2 (VSS[163]), U3.1C2 (VSS[163]), U3.1C4 (VSS[163]), U3.1C9 (VSS[163]), U3.1C13 (VSS[163]), U3.1C16 (VSS[163]), U3.1C21 (VSS[163]), U3.1D1 (VSS[163]), U3.1D3 (VSS[163]), U3.1D5 (VSS[163]), U3.1E2 (VSS[163]), U3.1E3 (VSS[163]), U3.1E5 (VSS[163]), U3.1E6 (VSS[163]), U3.1E10 (VSS[163]), U3.1E13 (VSS[163]), U3.1E16 (VSS[163])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
unnamed: AE1.1 (A), C350.1, R137.2
unnamed: L13.1, R146.2
unnamed: C43.2, C44.2, C45.2
unnamed: C48.2, C49.2, C50.2
unnamed: C53.2, C54.2, C55.2
unnamed: C59.2, C60.2, C61.2
unnamed: C64.2, C65.2, C66.2
unnamed: C99.1, R14.1, Y1.1
unnamed: C150.1, R40.2, Y2.1
unnamed: C308.1, C309.1
unnamed: D4.2 (A), J1.3, R21.2
unnamed: C172.1, D7.2 (A), R43.1, U4.2 (EN), U4.4 (IN)
unnamed: D17.2 (A), Q7.3 (D)
unnamed: D18.2 (A), J13.2, R166.2
unnamed: C374.1, D20.2 (A), R171.1, U33.2 (EN), U33.4 (IN)
unnamed: J3.SH (SHIELD), R57.1
unnamed: J4.SH (SHIELD), R58.1
unnamed: J7.SH, R116.1
unnamed: J11.52 (CLKREQ#), R154.1
unnamed: J11.50 (PERST#), R153.1
unnamed: C367.1, J11.14 (PERn0)
unnamed: C368.1, J11.16 (PERp0)
unnamed: J11.54 (PEWAKE#), R155.1
unnamed: J12.37 (GPIO26/SDIO_DAT2), R164.2
unnamed: L1.1, U2.50 (SW1), U2.51 (SW1)
unnamed: L2.1, U2.35 (SW2), U2.36 (SW2)
unnamed: LED1.2 (A), R15.2
unnamed: LED1.1 (K), Q1.3 (D)
unnamed: LED2.2 (A), R16.2
unnamed: LED3.1 (K), R147.1
unnamed: Q1.1 (G), R17.2, R18.1
unnamed: Q2.3 (D), R103.2, R104.2
unnamed: Q3.3 (D), R105.2, R106.2
unnamed: Q4.3 (D), R107.2, R108.2
unnamed: Q5.3 (D), R109.2, R110.2
unnamed: Q6.3 (D), R147.2
unnamed: Q6.1 (G), R148.2
unnamed: Q7.1 (G), R158.1
unnamed: C370.1, Q7.2 (S), U32.6 (VBACKUP)
unnamed: R3.2, R5.1
unnamed: R8.2, R9.1
unnamed: R10.2, R11.1
unnamed: R179.1, SW5.2
unnamed: R181.2, SW6.2
unnamed: L3.1, U2.55 (SW3)
unnamed: L4.1, U2.23 (SW4)
unnamed: L5.1, U2.45 (SW5)
unnamed: L6.1, U2.29 (SW6)
unnamed: L7.1, U2.42 (SW7)
unnamed: L8.1, U2.6 (SW8)
unnamed: L9.1, U2.68 (SW9)
unnamed: L10.1, U2.26 (SW10)
unnamed: NT1.1, U2.49 (VOUT1)
unnamed: NT2.1, U2.37 (VOUT2)
unnamed: NT3.1, U2.56 (VOUT3)
unnamed: NT4.1, U2.24 (VOUT4)
unnamed: NT5.1, U2.46 (VOUT5)
unnamed: NT6.1, U2.30 (VOUT6)
unnamed: NT7.1, U2.41 (VOUT7)
unnamed: NT8.1, U2.5 (VOUT8)
unnamed: NT9.1, U2.67 (VOUT9)
unnamed: NT10.1, U2.25 (VOUT10)
unnamed: C38.1, C39.1, R6.1, U2.4 (PWRON)
unnamed: C37.1, R2.2, R7.1, U2.32 (VDC)
unnamed: R4.1, U2.40 (~RESETB)
unnamed: R36.1, U3.2C2 (DDRPHY_PLL_AVSS)
unnamed: R38.1, U3.1R6 (ZQ_A)
unnamed: R37.1, U3.1J6 (ZQ_B)
unnamed: C100.1, U3.U28 (OSC_XIN), Y1.3
unnamed: R14.2, U3.U29 (OSC_XOUT)
unnamed: R20.1, U3.AA28 (UART0_RX_M0)
unnamed: R19.1, U3.1U24 (UART0_TX_M0)
unnamed: C160.1, U3.2N7 (MIPI_DCPHY_VREG)
unnamed: R40.1, R41.1, U3.AK5 (OSC_UFS_XIN)
unnamed: C149.1, R41.2, U3.AL5 (OSC_UFS_XOUT), Y2.3
unnamed: R32.1, U3.2R3 (USB2_OTG0_REXT)
unnamed: R31.1, U3.2P3 (USB2_OTG0_VBUSDET)
unnamed: R34.1, U3.2U8 (USB2_OTG1_REXT)
unnamed: R33.1, U3.2T10 (USB2_OTG1_VBUSDET)
unnamed: C173.1, R43.2, U4.5 (VCC)
unnamed: R51.1, R54.1
unnamed: R52.1, R56.1
unnamed: R59.1, R62.1
unnamed: R60.1, R64.1
unnamed: R67.2, R68.1, U17.2 (BPWR_DET)
unnamed: R70.1, U17.1 (RREF)
unnamed: R69.1, U17.45 (SCS)
unnamed: L11.2, U17.55 (V33_OUT)
unnamed: R82.2, U19.2 (MDIN0)
unnamed: R85.2, U19.5 (MDIN1)
unnamed: R89.2, U19.7 (MDIN2)
unnamed: R93.2, U19.10 (MDIN3)
unnamed: R81.2, U19.1 (MDIP0)
unnamed: R83.2, U19.4 (MDIP1)
unnamed: R87.2, U19.6 (MDIP2)
unnamed: R91.2, U19.9 (MDIP3)
unnamed: R75.1, U19.39 (RSET)
unnamed: R94.1, U19.26 (RXCTL/PHYAD2)
unnamed: R92.1, U19.27 (RXC/PHYAD1)
unnamed: R84.1, U19.25 (RXD0/RXDLY)
unnamed: R86.1, U19.24 (RXD1/TXDLY)
unnamed: R88.1, U19.23 (RXD2/PLLOFF)
unnamed: R90.1, U19.22 (RXD3/PHYAD0)
unnamed: R102.1, R112.1
unnamed: R115.1, U21.8 (OE)
unnamed: C336.1, U25.A9 (VDDi)
unnamed: C338.1, U25.A8 (VDDiQ2)
unnamed: C337.1, U25.A3 (VDDiQ)
unnamed: R118.2, R119.1, U26.4 (FB)
unnamed: R120.1, R122.1
unnamed: C351.1, R146.1, U30.3 (RF1)
unnamed: C349.1, R137.1, U30.1 (RF2)
unnamed: C352.1, L14.2
unnamed: C354.1, Y5.1
unnamed: C353.1, Y5.3
unnamed: R161.2, R162.1, R163.1, U32.1 (CLKOUT)
unnamed: C375.1, R171.2, U33.5 (VCC)
unnamed: C386.1, R176.2, U34.46 (VREG_AVDD)
unnamed: L15.2, U34.48 (VREG_LX)
unnamed: R180.1, R181.1, U35.1 (~CS)
VCC: R117.2, U25.B8 (VCC), U25.B9 (VCC), U25.C8 (VCC), U25.C9 (VCC), U25.E8 (VCC), U25.K8 (VCC), U25.N8 (VCC), U25.N9 (VCC), U25.P8 (VCC), U25.P9 (VCC)
VCC2V5_S0: C328.1, C329.1, C330.1, C331.1, C340.1, R117.1, R118.1, U26.5 (OUT)
VCC3V3_uSD: C342.1, C343.1, D16.2 (A), J8.4 (VDD)
VCC5V0_SYS: C3.1, C4.1, C28.1, C30.1, C31.1, C174.1, C175.1, C176.1, C189.1, C190.1, C201.1, C202.1, C232.1, C233.1, C234.1, C235.1, C315.1, C339.1, C361.1, C362.1, C363.1, C364.1, D19.2 (A), J9.29, J9.30, J10.29, J10.30, J13.1, J15.1, J15.2, R2.1, R67.1, U1.A2 (OUT), U1.A3 (OUT), U1.A4 (OUT), U1.B3 (OUT), U2.21 (VCCA), U2.64 (VCC12), U5.3 (VDD), U5.4 (VDD), U5.12 (VCONN), U5.13 (VCONN), U17.53 (SWR_V5_IN), U17.54 (LDO_V5_IN), U17.76 (SPWR_DET), U26.1 (IN), U26.3 (EN)
VCCA1V8_PLDO2_S0: C17.1, U2.58 (PLDO2)
VCCA1V8_PLDO6_S3: C23.1, U2.20 (VCCIO)
VCCA_1.8v_S0: C96.1, C98.1, C102.1, U3.2H12 (PLL_AVDD1V8), U3.2J10 (OSC_AVDD1V8), U3.2K11 (PMUIO0_VCC1V8)
VCCA_1V8_S0: C12.1, C106.1, C113.1, C124.1, C127.1, C141.1, C145.1, C146.1, C148.1, C154.1, C155.1, C159.1, C163.1, C166.1, C168.1, C170.1, R25.1, R26.1, R27.1, R28.1, U2.60 (PLDO1), U3.1W20 (MIPI_DPHY_CSI1/2_RX_AVDD1V8), U3.2A10 (SARADC_AVDD1V8), U3.2B10 (VCCIO3_VCC), U3.2D2 (DDRPHY_PLL_AVDD1V8), U3.2D12 (MIPI_DPHY_CSI3/4_RX_AVDD1V8), U3.2E12 (PCIE1_SATA1_USB3_OTG1_AVDD1V8), U3.2F12 (PCIE0_SATA0_AVDD1V8), U3.2M2 (OSC_UFS_AVDD), U3.2N4 (USB3_OTG0_DP_TX_AVDD1V8), U3.2N10 (HDMI_TX_EDP_TX_AVDDIO1V8), U3.2P2 (UFS_AVDD1V8), U3.2P4 (USB2_OTG_AVDD1V8), U3.2P8 (MIPI_DCPHY_AVDD1V8), U3.2P10 (HDMI_TX_EDP_TX_AVDDCMN1V8)
VCCA_1V8_S3: C108.1, C109.1, U3.2A4 (VCCIO5_VCC[2]), U3.2A5 (VCCIO5_VCC[2])
VCCA_3V3_S0: C29.1, C365.1, C366.1, J11.2 (3.3V), J11.4 (3.3V), J11.6 (3.3V), J11.8 (3.3V), J11.56 (3.3V), J11.58 (3.3V), R151.1, R152.1, U2.63 (PLDO4)
VCCIO_SD_S0: C36.1, C151.1, U2.65 (PLDO5), U3.2A8 (VCCIO1_VCC)
VCC_1V8_S3: C53.1, C54.1, C55.1, C266.1, C267.1, C268.1, C269.1, C306.1, C307.1, C344.1, C345.1, C355.1, C356.1, J10.26, L8.2, NT8.2, R1.1, R73.1, R74.1, R144.1, R149.1, R150.1, U18.C1 (VDD1), U18.C15 (VDD1), U18.W1 (VDD1), U18.W15 (VDD1), U19.28 (DVDD_RG)
VCC_2V0_PLDO_S3: C11.1, C41.1, C56.1, U2.9 (VCC14), U2.13 (VCC13), U2.59 (VCC11)
VCC_3.3v_S0: C103.1, R15.1, R16.1, U3.1U20 (PMUIO1_VCC)
VCC_3V3_S0: C25.1, C26.1, C27.1, C107.1, C110.1, C111.1, C125.1, C304.1, C305.1, C327.1, C341.1, C347.1, C348.1, C357.1, C358.1, C359.1, C360.1, C369.1, C379.1, C380.1, C381.1, C382.1, C383.1, C384.1, C385.1, C387.1, C390.1, C391.1, C392.1, J9.28, J10.27, J10.28, J15.3, J15.4, J16.1 (VCC), L4.2, NT4.2, R31.2, R33.2, R72.1, R113.1, R114.1, R159.1, R160.1, R161.1, R176.1, R178.1, R182.1, U3.2A2 (VCCIO2_VCC), U3.2A7 (VCCIO4_VCC), U3.2N3 (VCCIO6_VCC), U3.2P7 (USB2_OTG_AVDD3V3), U19.11 (AVDD33), U19.29 (DVDD33), U19.40 (AVDD33), U21.1 (VCCA), U32.7 (VDD), U34.1 (IOVDD), U34.11 (IOVDD), U34.20 (IOVDD), U34.30 (IOVDD), U34.38 (IOVDD), U34.44 (ADC_AVDD), U34.45 (IOVDD), U34.49 (VREG_VIN), U34.53 (USB_OTP_VDD), U34.54 (QSPI_IOVDD), U35.8 (VCC), U36.7 (VDD)
VDD2L_0V9_DDR_S3: C280.1, C281.1, C282.1, C283.1, C284.1, C295.1, C296.1, C297.1, C298.1, C299.1, U18.A6 (VDD2L), U18.A10 (VDD2L), U18.AA6 (VDD2L), U18.AA10 (VDD2L), U18.B6 (VDD2L), U18.B10 (VDD2L), U18.H2 (VDD2L), U18.H14 (VDD2L), U18.J2 (VDD2L), U18.J14 (VDD2L), U18.N2 (VDD2L), U18.N14 (VDD2L), U18.P2 (VDD2L), U18.P14 (VDD2L), U18.Y6 (VDD2L), U18.Y10 (VDD2L)
VDD2_DDR_S3: C59.1, C60.1, C61.1, C140.1, C238.1, C239.1, C240.1, C241.1, C242.1, C243.1, C244.1, C245.1, C246.1, C247.1, C248.1, C249.1, C250.1, C251.1, C252.1, C253.1, C254.1, C255.1, C256.1, C257.1, C258.1, C259.1, C260.1, C261.1, C262.1, C263.1, C264.1, C265.1, L9.2, NT9.2, R10.1, U3.2B2 (DDRPHY_CKE_VDDQ), U18.A7 (VDD2H), U18.A8 (VDD2H), U18.A9 (VDD2H), U18.AA7 (VDD2H), U18.AA8 (VDD2H), U18.AA9 (VDD2H), U18.B7 (VDD2H), U18.B9 (VDD2H), U18.C7 (VDD2H), U18.C9 (VDD2H), U18.D8 (VDD2H), U18.E7 (VDD2H), U18.E9 (VDD2H), U18.F6 (VDD2H), U18.F7 (VDD2H), U18.F9 (VDD2H), U18.F10 (VDD2H), U18.J5 (VDD2H), U18.J11 (VDD2H), U18.K1 (VDD2H), U18.K2 (VDD2H), U18.K3 (VDD2H), U18.K4 (VDD2H), U18.K5 (VDD2H), U18.K6 (VDD2H), U18.K10 (VDD2H), U18.K11 (VDD2H), U18.K12 (VDD2H), U18.K13 (VDD2H), U18.K14 (VDD2H), U18.K15 (VDD2H), U18.L6 (VDD2H), U18.L7 (VDD2H), U18.L8 (VDD2H), U18.L9 (VDD2H), U18.L10 (VDD2H), U18.M1 (VDD2H), U18.M2 (VDD2H), U18.M3 (VDD2H), U18.M4 (VDD2H), U18.M5 (VDD2H), U18.M6 (VDD2H), U18.M10 (VDD2H), U18.M11 (VDD2H), U18.M12 (VDD2H), U18.M13 (VDD2H), U18.M14 (VDD2H), U18.M15 (VDD2H), U18.N5 (VDD2H), U18.N11 (VDD2H), U18.T6 (VDD2H), U18.T7 (VDD2H), U18.T9 (VDD2H), U18.T10 (VDD2H), U18.U7 (VDD2H), U18.U9 (VDD2H), U18.V8 (VDD2H), U18.W7 (VDD2H), U18.W9 (VDD2H), U18.Y7 (VDD2H), U18.Y9 (VDD2H)
VDDA0V75_HDMI_S0: C51.1, C152.1, C153.1, U2.11 (NLDO3), U3.2N11 (HDMI_TX_EDP_TX_AVDDD0V75), U3.2P11 (HDMI_TX_EDP_TX_AVDDC0V75)
VDDA_0.75v_S0: C101.1, U3.2G11 (PLL_DVDD0V75)
VDDA_0V75_S0: C62.1, C114.1, C123.1, C156.1, C157.1, C161.1, C162.1, C164.1, C165.1, U2.8 (NLDO5), U3.2D11 (MIPI_DPHY_CSI3/4_RX_AVDD0V75), U3.2H11 (OTP_DVDD0V75), U3.2L11 (MIPI_DPHY_CSI1/2_RX_AVDD0V75), U3.2M7 (MIPI_DCPHY_AVDD), U3.2P5 (USB2_OTG_DVDD0V75)
VDDA_0V85_S0: C57.1, C126.1, C143.1, C144.1, C167.1, C169.1, U2.10 (NLDO4), U3.2E11 (PCIE1_SATA1_USB3_OTG1_AVDD0V85), U3.2F11 (PCIE0_SATA0_AVDD0V85), U3.2M5 (USB3_OTG0_DP_TX_AVDD0V85), U3.2N2 (UFS_AVDD0V85), U3.2N5 (USB3_OTG0_DP_TX_DVDD0V85)
VDDA_1V2_S0: C22.1, C147.1, C158.1, C332.1, C333.1, C334.1, C335.1, U2.57 (PLDO3), U3.2M3 (VCCIO7_VCC), U3.2M8 (MIPI_DCPHY_AVDD1V2), U25.A4 (VCCQ), U25.A5 (VCCQ), U25.B4 (VCCQ), U25.B5 (VCCQ), U25.C4 (VCCQ), U25.C5 (VCCQ), U25.E5 (VCCQ), U25.F5 (VCCQ)
VDDA_DDR_PLL_S0: C46.1, C142.1, U2.12 (NLDO2), U3.2C3 (DDRPHY_PLL_DVDD)
VDDQ_DDR_S0: C43.1, C44.1, C45.1, C128.1, C129.1, C130.1, C131.1, C132.1, C133.1, C270.1, C271.1, C272.1, C273.1, C274.1, C275.1, C276.1, C277.1, C278.1, C279.1, C285.1, C286.1, C287.1, C288.1, C289.1, C290.1, C291.1, C292.1, C293.1, C294.1, L6.2, NT6.2, R8.1, R37.2, R38.2, U3.2D1 (DDRPHY_CK_VDDQ), U3.2E1 (DDRPHY_VDDQ[6]), U3.2F1 (DDRPHY_VDDQ[6]), U3.2F2 (DDRPHY_VDDQ[6]), U3.2G1 (DDRPHY_VDDQ[6]), U3.2H1 (DDRPHY_VDDQ[6]), U3.2J2 (DDRPHY_VDDQ[6]), U18.A3 (VDDQ), U18.A13 (VDDQ), U18.AA3 (VDDQ), U18.AA13 (VDDQ), U18.B2 (VDDQ), U18.B14 (VDDQ), U18.C3 (VDDQ), U18.C13 (VDDQ), U18.D4 (VDDQ), U18.D12 (VDDQ), U18.E5 (VDDQ), U18.E11 (VDDQ), U18.F1 (VDDQ), U18.F3 (VDDQ), U18.F4 (VDDQ), U18.F12 (VDDQ), U18.F13 (VDDQ), U18.F15 (VDDQ), U18.G1 (VDDQ), U18.G2 (VDDQ), U18.G14 (VDDQ), U18.G15 (VDDQ), U18.R1 (VDDQ), U18.R2 (VDDQ), U18.R14 (VDDQ), U18.R15 (VDDQ), U18.T1 (VDDQ), U18.T3 (VDDQ), U18.T4 (VDDQ), U18.T12 (VDDQ), U18.T13 (VDDQ), U18.T15 (VDDQ), U18.U5 (VDDQ), U18.U11 (VDDQ), U18.V4 (VDDQ), U18.V12 (VDDQ), U18.W3 (VDDQ), U18.W13 (VDDQ), U18.Y2 (VDDQ), U18.Y14 (VDDQ)
VDD_0V75_S3: C42.1, U2.14 (NLDO1)
VDD_3.3v_S3: C104.1, C105.1, U3.2L2 (PMU_LOGIC_DVDD0V75[2]), U3.2L10 (PMU_LOGIC_DVDD0V75[2])
VDD_CPU_BIG_S0: C8.1, C9.1, C10.1, C71.1, C72.1, C73.1, C74.1, C75.1, C76.1, C77.1, C78.1, L1.2, NT1.2, U3.2G5 (CPU_BIG_DVDD[8]), U3.2G6 (CPU_BIG_DVDD[8]), U3.2H6 (CPU_BIG_DVDD[8]), U3.2H7 (CPU_BIG_DVDD[8]), U3.2J6 (CPU_BIG_DVDD[8]), U3.2J7 (CPU_BIG_DVDD[8]), U3.2K6 (CPU_BIG_DVDD[8]), U3.2K7 (CPU_BIG_DVDD[8])
VDD_CPU_LIT_S0: C19.1, C20.1, C21.1, C67.1, C68.1, C69.1, C70.1, L3.2, NT3.2, U3.2H4 (CPU_LIT_DVDD[5]), U3.2J3 (CPU_LIT_DVDD[5]), U3.2J4 (CPU_LIT_DVDD[5]), U3.2K3 (CPU_LIT_DVDD[5]), U3.2K4 (CPU_LIT_DVDD[5])
VDD_DDR_S0: C64.1, C65.1, C66.1, C134.1, C135.1, C136.1, C137.1, C138.1, C139.1, L10.2, NT10.2, U3.2E2 (DDRPHY_DVDD[5]), U3.2F3 (DDRPHY_DVDD[5]), U3.2G2 (DDRPHY_DVDD[5]), U3.2G3 (DDRPHY_DVDD[5]), U3.2H2 (DDRPHY_DVDD[5])
VDD_GPU_S0: C33.1, C34.1, C35.1, C92.1, C93.1, C94.1, C95.1, L5.2, NT5.2, R3.1, U3.2C4 (GPU_DVDD[5]), U3.2C5 (GPU_DVDD[5]), U3.2D4 (GPU_DVDD[5]), U3.2D5 (GPU_DVDD[5]), U3.2E4 (GPU_DVDD[5])
VDD_LOGIC_S0: C48.1, C49.1, C50.1, C79.1, C80.1, C81.1, C82.1, C83.1, C84.1, C85.1, C86.1, L7.2, NT7.2, U3.2E7 (LOGIC_DVDD[7]), U3.2F7 (LOGIC_MEM_DVDD[2]), U3.2F8 (LOGIC_DVDD[7]), U3.2F9 (LOGIC_DVDD[7]), U3.2G8 (LOGIC_DVDD[7]), U3.2G9 (LOGIC_DVDD[7]), U3.2H8 (LOGIC_DVDD[7]), U3.2H9 (LOGIC_DVDD[7]), U3.2J9 (LOGIC_MEM_DVDD[2])
VDD_NPU_S0: C14.1, C15.1, C16.1, C87.1, C88.1, C89.1, C90.1, C91.1, L2.2, NT2.2, U3.2C7 (NPU_DVDD[5]), U3.2C8 (NPU_DVDD[5]), U3.2C9 (NPU_DVDD[5]), U3.2D7 (NPU_DVDD[5]), U3.2D8 (NPU_DVDD[5])
Vbus_USB_{HOST1}: C191.1, D10.2 (A), J3.1 (VBUS1)
Vbus_USB_{HOST2}: C204.1, D13.2 (A), J3.10 (VBUS2)
Vbus_USB_{HOST3}: C192.1, D11.2 (A), J4.1 (VBUS1)
Vbus_USB_{HOST4}: C203.1, D12.2 (A), J4.10 (VBUS2)
Vbus_USB_{MCU}: C5.1, C6.1, C373.1, R172.1, U1.B4 (IN2), U1.B5 (IN2), U1.C4 (IN2), U1.C5 (IN2), U33.3 (OUT)
Vbus_USB_{OTG}: C1.1, C2.1, C171.1, R44.1, U1.B1 (IN1), U1.B2 (IN1), U1.C1 (IN1), U1.C2 (IN1), U4.3 (OUT), U5.2 (VBUS)
